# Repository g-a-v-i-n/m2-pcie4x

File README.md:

# M.2 -> PCIe 4x Adapter

🚧 Under Construction 🚧

This is a design for an adapter that provides one extra PCIe 4x interface to any motherboard with an MGFF M key M.2 interface. It is designed to cleanly extend a mini-ITX form factor motherboard, with the end result being a sort of hybrid between mini-ITX and micro-ATX.

Made with kicad.

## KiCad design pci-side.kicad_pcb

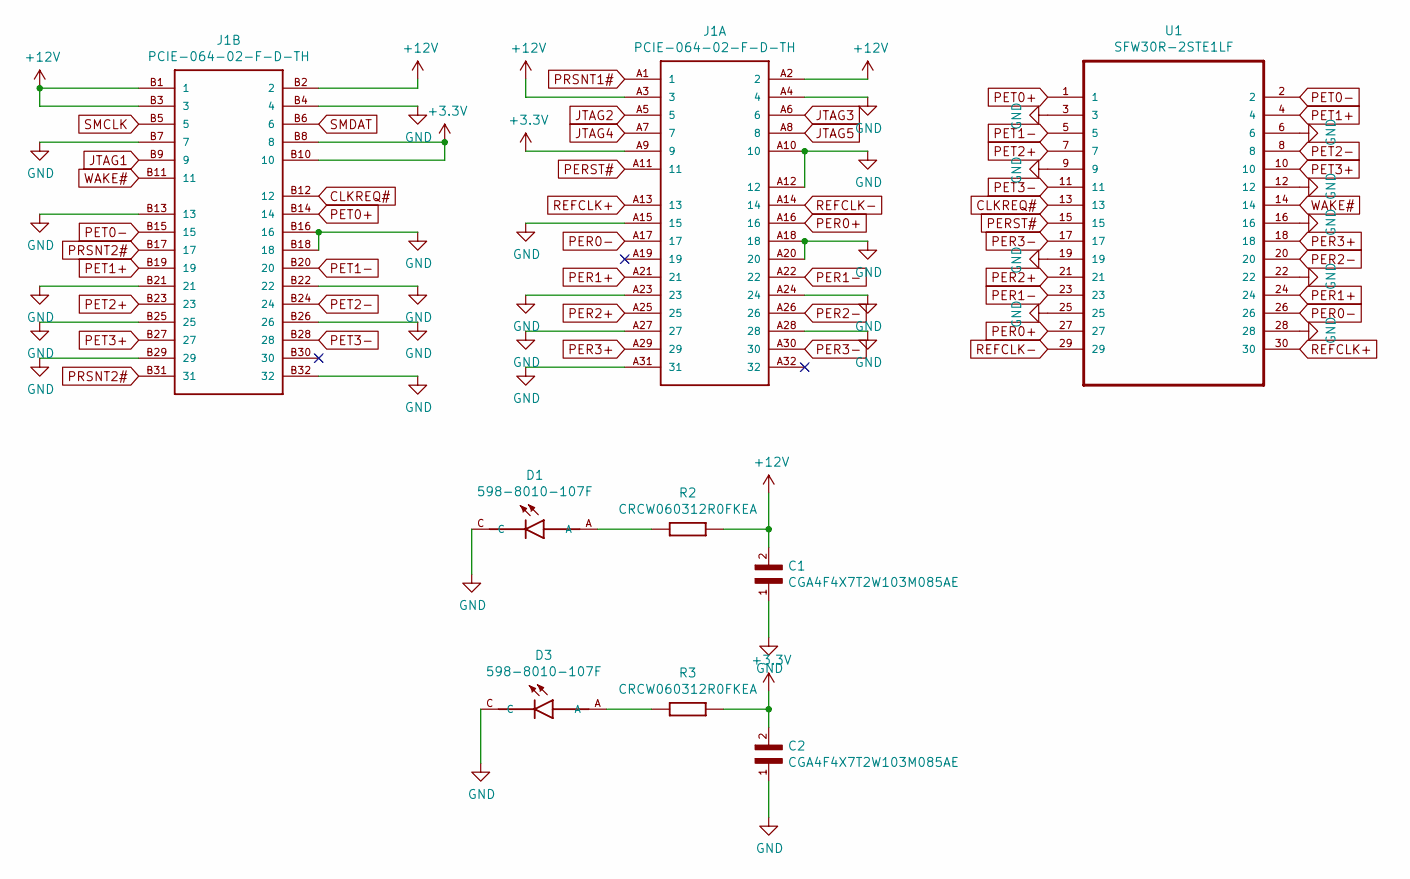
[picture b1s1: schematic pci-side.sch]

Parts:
C1, C2: CGA4F4X7T2W103M085AE; CAPC2012X100N
D1, D3: 598-8010-107F; LEDSC160X80X70L45N
J1: PCIE-064-02-F-D-TH; SAMTEC_PCIE-064-02-F-D-TH
R2, R3: CRCW060312R0FKEA; 0603
U1: SFW30R-2STE1LF; FCI_SFW30R-2STE1LF

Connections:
+3V3: C2.2, J1.A9 (9), J1.B8 (8), J1.B10 (10), R3.2
+12V: C1.2, J1.A2 (2), J1.A3 (3), J1.B1 (1), J1.B2 (2), J1.B3 (3), R2.2
CLKREQ#: J1.B12 (12), U1.13
GND: C1.1, C2.1, D1.C, D3.C, J1.A4 (4), J1.A10 (10), J1.A12 (12), J1.A15 (15), J1.A18 (18), J1.A20 (20), J1.A23 (23), J1.A24 (24), J1.A27 (27), J1.A28 (28), J1.A31 (31), J1.B4 (4), J1.B7 (7), J1.B13 (13), J1.B16 (16), J1.B18 (18), J1.B21 (21), J1.B22 (22), J1.B25 (25), J1.B26 (26), J1.B29 (29), J1.B32 (32), U1.3, U1.6, U1.9, U1.12, U1.16, U1.19, U1.22, U1.25, U1.28
JTAG1: J1.B9 (9)
JTAG2: J1.A5 (5)
JTAG3: J1.A6 (6)
JTAG4: J1.A7 (7)
JTAG5: J1.A8 (8)
unnamed: D1.A, R2.1
unnamed: D3.A, R3.1
PER0+: J1.A16 (16), U1.27
PER0-: J1.A17 (17), U1.26
PER1+: J1.A21 (21), U1.24
PER1-: J1.A22 (22), U1.23
PER2+: J1.A25 (25), U1.21
PER2-: J1.A26 (26), U1.20
PER3+: J1.A29 (29), U1.18
PER3-: J1.A30 (30), U1.17
PERST#: J1.A11 (11), U1.15
PET0+: J1.B14 (14), U1.1
PET0-: J1.B15 (15), U1.2
PET1+: J1.B19 (19), U1.4
PET1-: J1.B20 (20), U1.5
PET2+: J1.B23 (23), U1.7
PET2-: J1.B24 (24), U1.8
PET3+: J1.B27 (27), U1.10
PET3-: J1.B28 (28), U1.11
PRSNT1#: J1.A1 (1)
PRSNT2#: J1.B17 (17), J1.B31 (31)
REFCLK+: J1.A13 (13), U1.30
REFCLK-: J1.A14 (14), U1.29
SMCLK: J1.B5 (5)
SMDAT: J1.B6 (6)
WAKE#: J1.B11 (11), U1.14

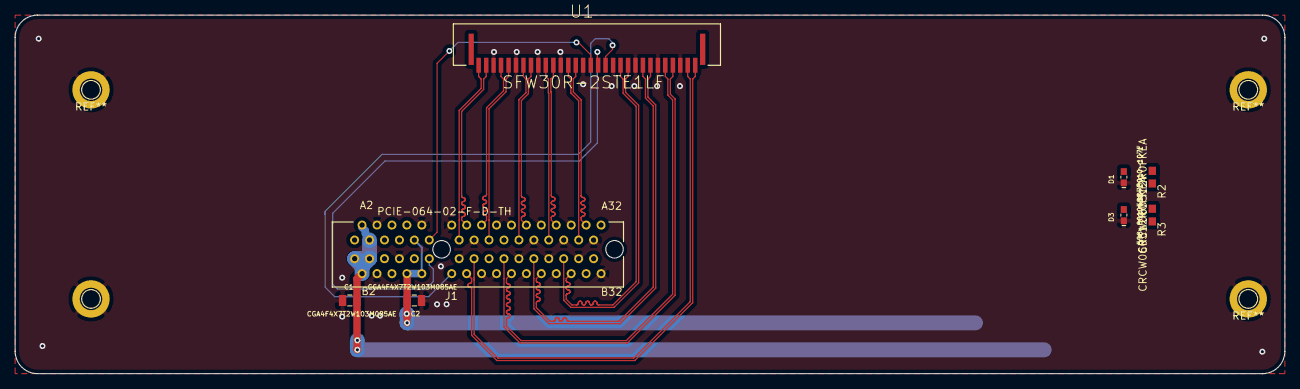
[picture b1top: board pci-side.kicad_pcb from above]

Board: 2 copper layers, 170.0 x 48.0 mm, 8 parts (0 on the bottom side), 27 nets.

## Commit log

2019-08-15 mechanical placement
2019-08-17 rename, incl libs
2019-08-17 readme changes
2019-08-17 gitignore how-to-import, add gerber folder
2019-08-17 rename board 1 files
2019-08-18 remove annoying htm files
2019-08-20 better dPair routing, follow spec, move svg
